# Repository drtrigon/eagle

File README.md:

## Projekte

Results of eagle and kicad CI from travis are stored in https://github.com/drtrigon/eagle/tree/result/pcb branch and linked/shown in https://github.com/drtrigon/sketchbook repo. See there and in [.travis.yml](.travis.yml) for more info.

(might make sense to split projects off into separate repos/submodules)

### N64TinyUSB

Order: make sure to select PCB Thickness 2mm and "Gold Fingers"!

based on boxtec.ch Helvetiny 1.0 PCB design:
* https://github.com/boxtec/helvetiny85
* https://playground.boxtec.ch/doku.php/arduino/attinyusb/helvetiny85

#### code/firmware (design based on attiny45 n64-usb)

Built using the attiny45 n64-usb AVR source files. Works out of the box but emulates 1 device only (that contains both controller).

https://github.com/drtrigon/sketchbook/tree/master/cli/n64dual_tiny45

#### Hint: Order PCB directly

Upload the GERBER files below to https://jlcpcb.com/quote and order.

* Helvetiny85: https://github.com/drtrigon/eagle/blob/master/projects/HelveTiny_1.0_GERBER.zip
* Floweronly Arduino Shield: https://github.com/boxtec/floweronly/blob/master/floweronly_v1.0_GERBER.zip

### Drone_MultiWii / FlightController

### arduino-papilio_1-WireSniffer_Rev1

### DACRackUnit

## Setup

I would like to use features like CI (continous integration) keep a copy/mirror on e.g. github and more.

Maintaining a copy/mirror (more precise: with 2 remotes overloaded origin) on GitHub also allows
to use GitLab and GitHub together and by that all the nice featurs on GitHub.
See also; https://steveperkins.com/migrating-projects-from-github-to-gitlab/

"Option 2: Overload Origin with Both Remotes (needs one single pull/push only)"; in order to clone
and set this repo up use:
```
$ git clone file://///data/mount/gvfs/smb-share:server=.../01git/eagle.git
$ cd eagle
$ git remote set-url --add origin https://github.com/drtrigon/eagle.git
```
you can check the settings with:
```
$ git remote -v
origin  /data/mount/gvfs/smb-share:server=.../01git/eagle.git/ (fetch)
origin  /data/mount/gvfs/smb-share:server=.../01git/eagle.git/ (push)
origin  https://github.com/drtrigon/eagle.git (push)
```

### Enable EDRC.ME for a Repository (for Eagle)
http://www.edrc.me/docs/

### Enable Travis CI for a Repository (for Eagle)
https://github.com/drtrigon/test-eagle-edrc/blob/master/.travis.yml (does not work reliably yet)

Login to Travis-CI using the GitHub account and enable Travis-CI for the given repo.

Add a .travis.yml file to your project, commit, pull/push and enjoy.

A word of caution; the travis run will at the end - if successfull - try to push the
results back to this repo.

### Further Info
EDRC.me: https://michaelblouin.ca/blog/2018/02/25/automate-design-rule-checks-autodesk-eagle/

gerber (travis or local python script): http://www.rocketnumbernine.com/2011/12/14/automating-gerbers-from-eagle
```
...
# create top copper (cmp), bottom copper (sol), top solder mask (stc), bottom solder mask (sts), {top} silkscreen (plc)
${EAGLE} -X -dGERBER_RS274X -o${outputfile}.cmp ${board} Top Pads Vias
${EAGLE} -X -dGERBER_RS274X -o${outputfile}.sol ${board} Bottom Pads Vias
#${EAGLE} -X -dGERBER_RS274X -o${outputfile}.mil ${board} Milling
${EAGLE} -X -dGERBER_RS274X -o${outputfile}.plc ${board} Dimension tPlace tNames
${EAGLE} -X -dGERBER_RS274X -o${outputfile}.stc ${board} tStop
${EAGLE} -X -dGERBER_RS274X -o${outputfile}.sts ${board} bStop
#${EAGLE} -X -dGERBER_RS274X -o${outputfile}.crc ${board} tCream
#${EAGLE} -X -dGERBER_RS274X -o${outputfile}.dpv ${board} Drills
#${EAGLE} -X -dGERBER_RS274X -o${outputfile}.drh ${board} Holes
...
```
(mill and drill needs: gerb274x-mill-drill.cam)

#### Generate schematic, PCB and GERBER from KiCAD (TODO)
* https://forum.kicad.info/t/generate-gerber-files-from-script/1853/15
* https://electronics.stackexchange.com/questions/390135/command-line-interface-for-kicad

## License

The content of this project itself is licensed under the [Creative Commons Attribution 3.0 license](http://creativecommons.org/licenses/by/3.0/us/deed.en_US), and the underlying source code used to format and display that content is licensed under the [MIT license](http://opensource.org/licenses/mit-license.php), see the [LICENSE](LICENSE.md) file for license rights and limitations (MIT).

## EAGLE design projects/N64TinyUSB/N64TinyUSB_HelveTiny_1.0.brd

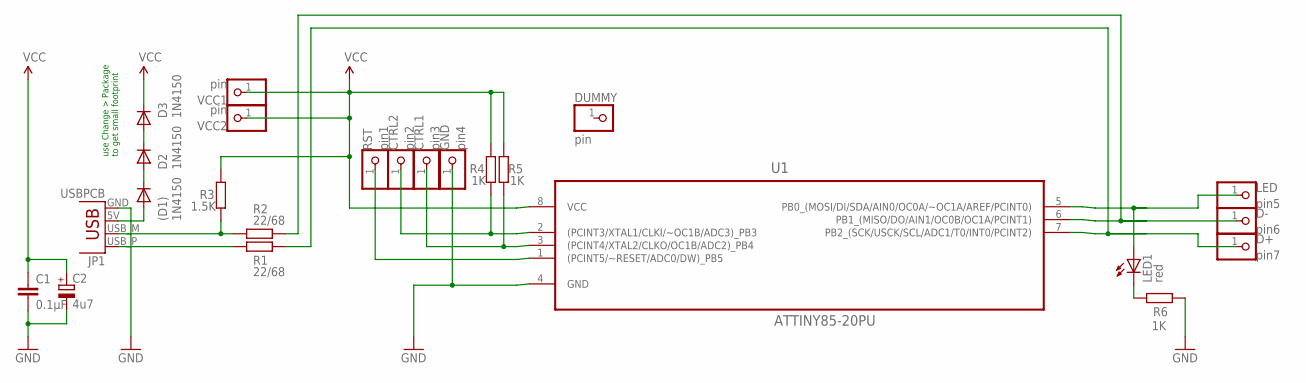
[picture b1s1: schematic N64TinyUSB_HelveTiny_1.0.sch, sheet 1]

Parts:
(D1): 1N4150; D-2.5
C1: 0.1μF; C025-024X044
C2: 4u7; E2,5-6E
CTRL1: pin3; 1X01
CTRL2: pin2; 1X01
D2, D3: 1N4150; D-2.5
D+: pin7; 1X01
D-: pin6; 1X01
DUMMY: pin; 1X01
GND: pin4; 1X01
JP1: USBPCB; USB-A-PCB
LED: pin5; 1X01
LED1: red; LED3MM
R1, R2: 22/68; 0207/7
R3: 1.5K; 0207/7
R4, R5, R6: 1K; 0207/7
RST: pin1; 1X01
U1: ATTINY85-20PU; DIP254P762X533-8
VCC1, VCC2: pin; 1X01

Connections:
CTRL1: CTRL1.1, R5.1, U1.3 ((PCINT4/XTAL2/CLKO/OC1B/ADC2)_PB4)
CTRL2: CTRL2.1, R4.1, U1.2 ((PCINT3/XTAL1/CLKI/~OC1B/ADC3)_PB3)
GND: C1.2, C2.-, GND.1, JP1.GND, R6.1, U1.4 (GND)
unnamed: JP1.USB_M (D-), R2.1, R3.1
unnamed: JP1.USB_P (D+), R1.1
unnamed: LED.1, LED1.A, U1.5 (PB0_(MOSI/DI/SDA/AIN0/OC0A/~OC1A/AREF/P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)
unnamed: D-.1, R2.2, U1.6 (PB1_(MISO/DO/AIN1/OC0B/OC1A/PCINT1))
unnamed: D+.1, R1.2, U1.7 (PB2_(SCK/USCK/SCL/ADC1/T0/INT0/PCINT2))
unnamed: (D1).A, JP1.5V (VBUS)
unnamed: (D1).C, D2.A
unnamed: D2.C, D3.A
unnamed: LED1.K (C), R6.2
RST: RST.1, U1.1 ((PCINT5/~RESET/ADC0/DW)_PB5)
VCC: C1.1, C2.+, D3.C, R3.2, R4.2, R5.2, U1.8 (VCC), VCC1.1, VCC2.1

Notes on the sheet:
use Change > Package to get small footprint

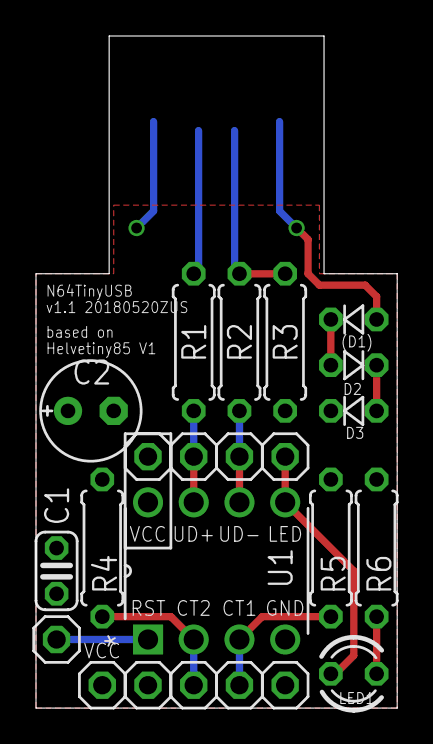
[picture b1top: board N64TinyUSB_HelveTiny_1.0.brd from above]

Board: 2 copper layers, 20.1 x 37.3 mm, 24 parts (1 on the bottom side), 14 nets.

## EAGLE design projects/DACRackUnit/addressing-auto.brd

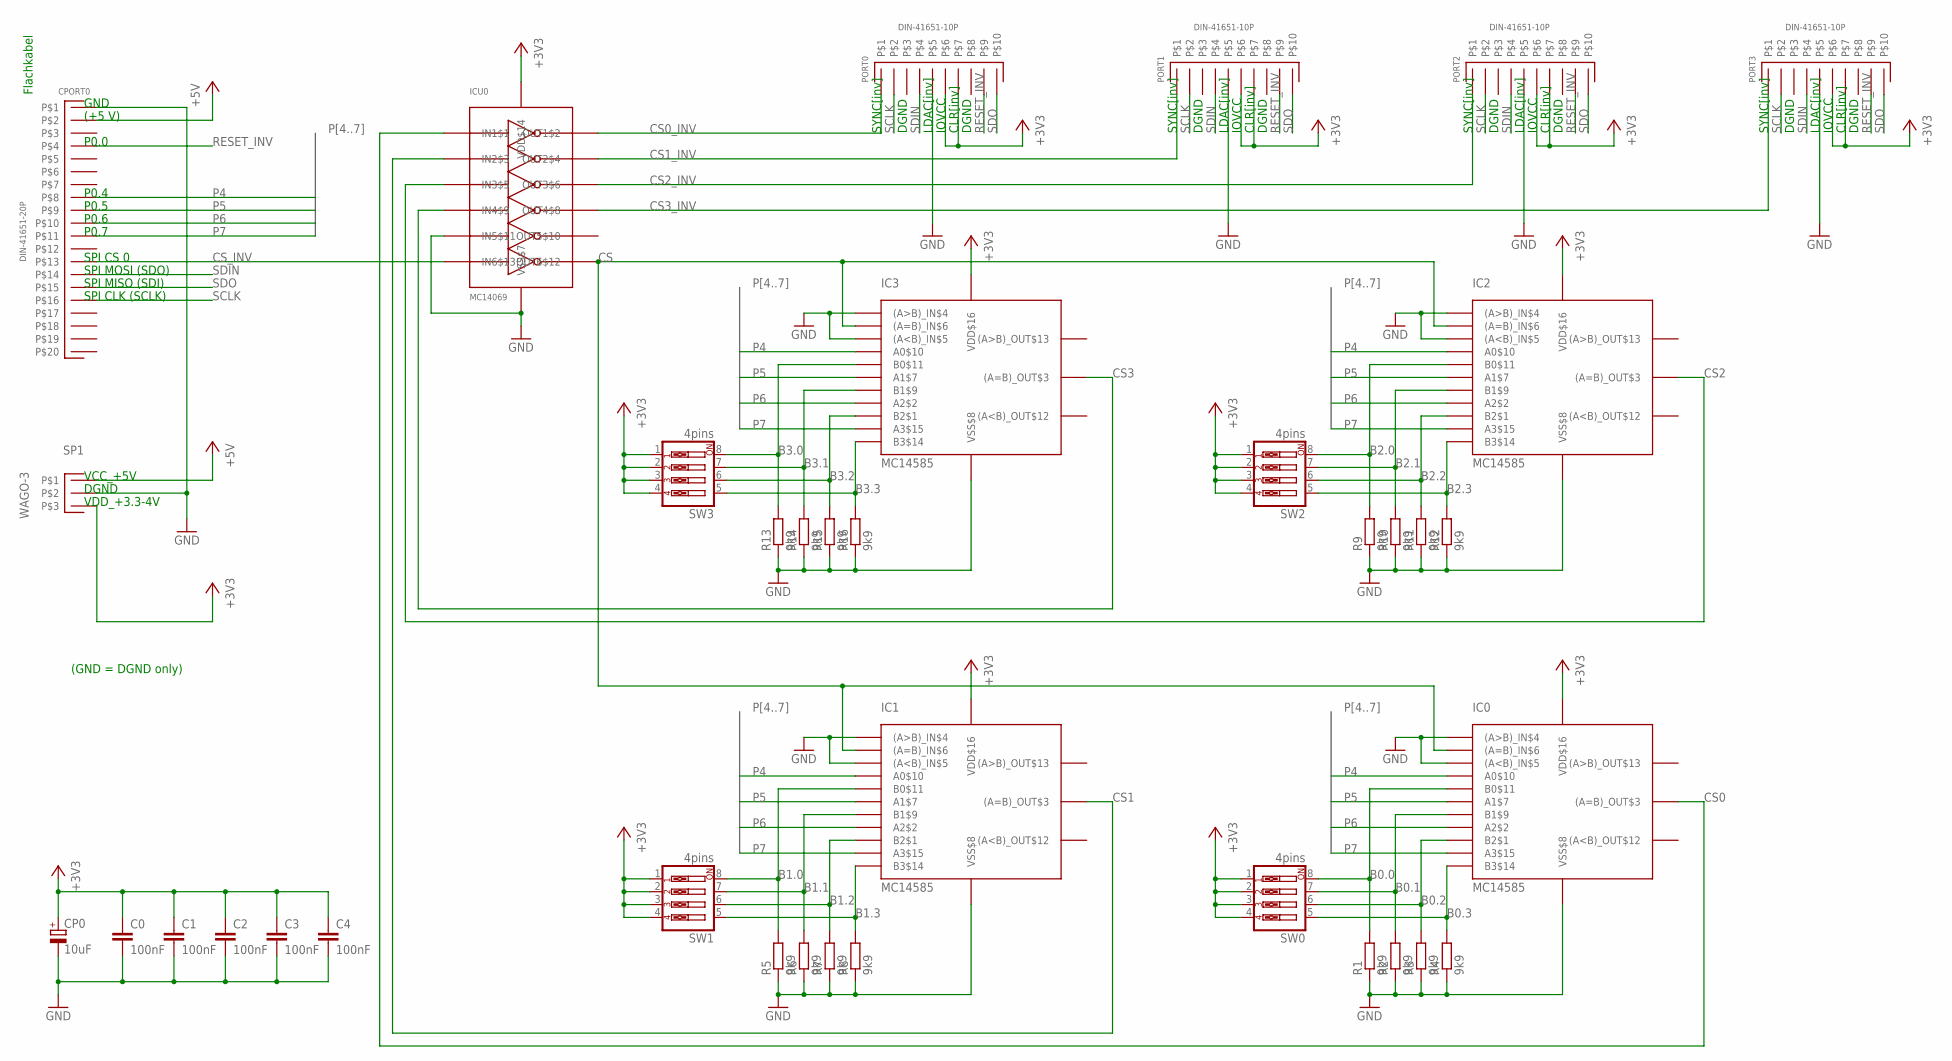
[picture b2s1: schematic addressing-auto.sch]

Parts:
C0, C1, C2, C3, C4: 100nF; C075-032X103
CP0: 10uF; B45181B
CPORT0: DIN-41651-20P
IC0, IC1, IC2, IC3: MC14585; PDIP-16
ICU0: MC14069; PDIP-14
PORT0, PORT1, PORT2, PORT3: DIN-41651-10P
R1, R2, R3, R4, R5, R6, R7, R8, R9, R10, R11, R12, R13, R14, R15, R16: 9k9; 0207/12
SP1: WAGO-3
SW0, SW1, SW2, SW3: 4pins; EDG-04

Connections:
+3V3: C0.1, C1.1, C2.1, C3.1, C4.1, CP0.+, IC0.VDD$16, IC1.VDD$16, IC2.VDD$16, IC3.VDD$16, ICU0.VDD$14, PORT0.P$6, PORT0.P$7, PORT1.P$6, PORT1.P$7, PORT2.P$6, PORT2.P$7, PORT3.P$6, PORT3.P$7, SP1.P$3, SW0.1, SW0.2, SW0.3, SW0.4, SW1.1, SW1.2, SW1.3, SW1.4, SW2.1, SW2.2, SW2.3, SW2.4, SW3.1, SW3.2, SW3.3, SW3.4
+5V: CPORT0.P$2, SP1.P$1
B0.0: IC0.B0$11, R1.2, SW0.8
B0.1: IC0.B1$9, R2.2, SW0.7
B0.2: IC0.B2$1, R3.2, SW0.6
B0.3: IC0.B3$14, R4.2, SW0.5
B1.0: IC1.B0$11, R5.2, SW1.8
B1.1: IC1.B1$9, R6.2, SW1.7
B1.2: IC1.B2$1, R7.2, SW1.6
B1.3: IC1.B3$14, R8.2, SW1.5
B2.0: IC2.B0$11, R9.2, SW2.8
B2.1: IC2.B1$9, R10.2, SW2.7
B2.2: IC2.B2$1, R11.2, SW2.6
B2.3: IC2.B3$14, R12.2, SW2.5
B3.0: IC3.B0$11, R13.2, SW3.8
B3.1: IC3.B1$9, R14.2, SW3.7
B3.2: IC3.B2$1, R15.2, SW3.6
B3.3: IC3.B3$14, R16.2, SW3.5
CS: IC0.(A=B)_IN$6, IC1.(A=B)_IN$6, IC2.(A=B)_IN$6, IC3.(A=B)_IN$6, ICU0.OUT6$12
CS0: IC0.(A=B)_OUT$3, ICU0.IN1$1
CS0_INV: ICU0.OUT1$2, PORT0.P$1
CS1: IC1.(A=B)_OUT$3, ICU0.IN2$3
CS1_INV: ICU0.OUT2$4, PORT1.P$1
CS2: IC2.(A=B)_OUT$3, ICU0.IN3$5
CS2_INV: ICU0.OUT3$6, PORT2.P$1
CS3: IC3.(A=B)_OUT$3, ICU0.IN4$9
CS3_INV: ICU0.OUT4$8, PORT3.P$1
CS_INV: CPORT0.P$13, ICU0.IN6$13
GND: C0.2, C1.2, C2.2, C3.2, C4.2, CP0.-, CPORT0.P$1, IC0.(A<B)_IN$5, IC0.(A>B)_IN$4, IC0.VSS$8, IC1.(A<B)_IN$5, IC1.(A>B)_IN$4, IC1.VSS$8, IC2.(A<B)_IN$5, IC2.(A>B)_IN$4, IC2.VSS$8, IC3.(A<B)_IN$5, IC3.(A>B)_IN$4, IC3.VSS$8, ICU0.IN5$11, ICU0.VSS$7, PORT0.P$5, PORT1.P$5, PORT2.P$5, PORT3.P$5, R1.1, R2.1, R3.1, R4.1, R5.1, R6.1, R7.1, R8.1, R9.1, R10.1, R11.1, R12.1, R13.1, R14.1, R15.1, R16.1, SP1.P$2
P4: CPORT0.P$8, IC0.A0$10, IC1.A0$10, IC2.A0$10, IC3.A0$10
P5: CPORT0.P$9, IC0.A1$7, IC1.A1$7, IC2.A1$7, IC3.A1$7
P6: CPORT0.P$10, IC0.A2$2, IC1.A2$2, IC2.A2$2, IC3.A2$2
P7: CPORT0.P$11, IC0.A3$15, IC1.A3$15, IC2.A3$15, IC3.A3$15
RESET_INV: CPORT0.P$4, PORT0.P$9, PORT1.P$9, PORT2.P$9, PORT3.P$9
SCLK: CPORT0.P$16, PORT0.P$2, PORT1.P$2, PORT2.P$2, PORT3.P$2
SDIN: CPORT0.P$14, PORT0.P$4, PORT1.P$4, PORT2.P$4, PORT3.P$4
SDO: CPORT0.P$15, PORT0.P$10, PORT1.P$10, PORT2.P$10, PORT3.P$10

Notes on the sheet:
GND
(+5 V)
P0.0
P0.4
P0.5
P0.6
P0.7
SPI CS 0
SPI MOSI (SDO)
SPI MISO (SDI)
SPI CLK (SCLK)
SYNC[inv]
DGND
LDAC[inv]
IOVCC
CLR[inv]
VCC_+5V
VDD_+3.3-4V
(GND = DGND only)
Flachkabel

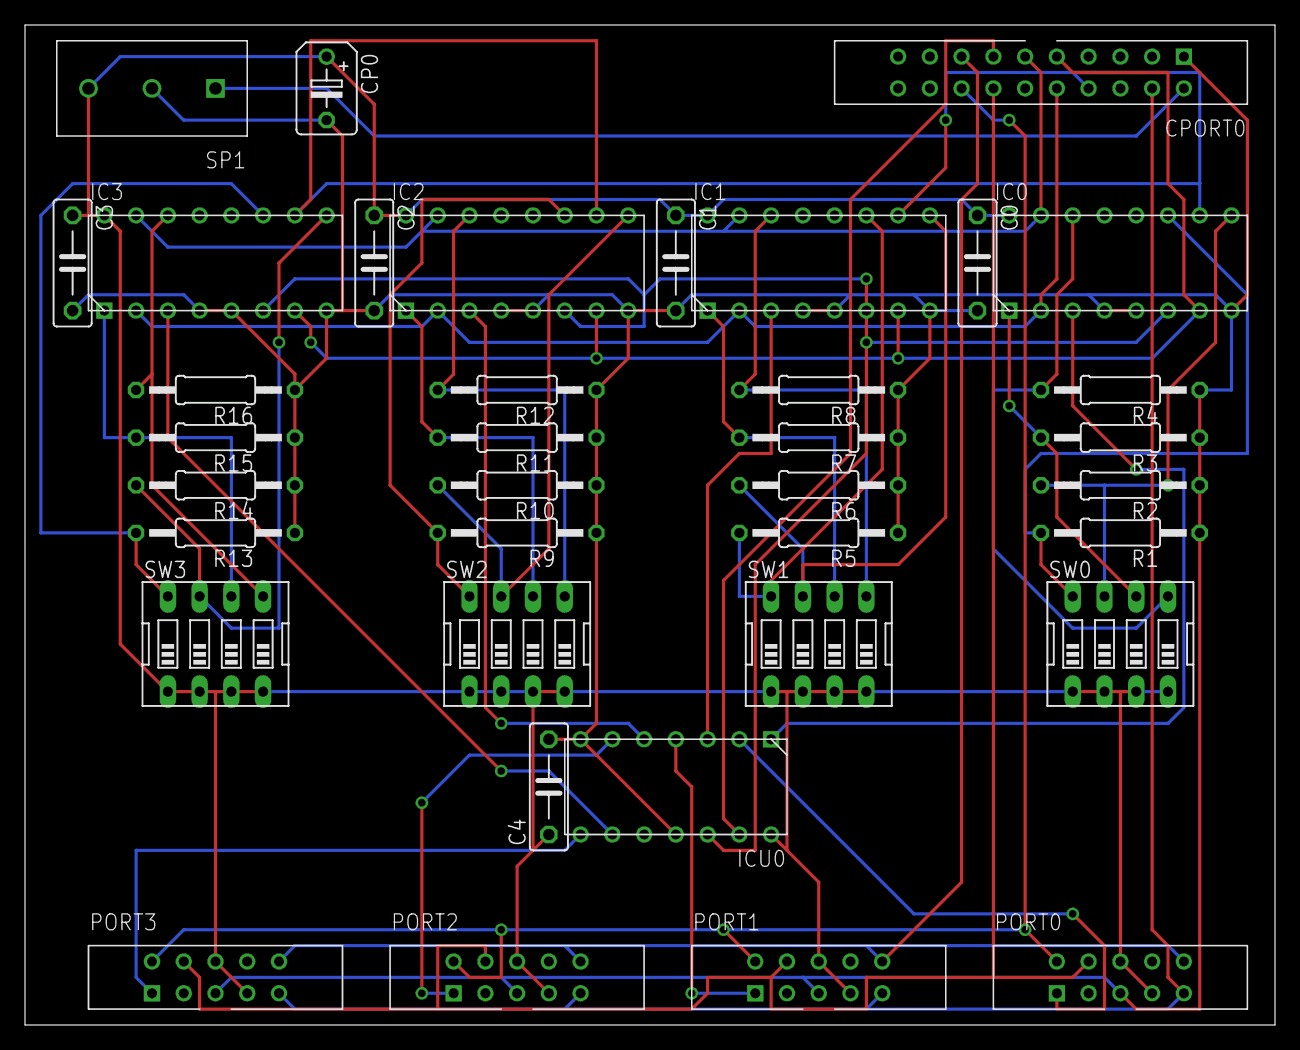
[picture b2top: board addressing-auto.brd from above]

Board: 2 copper layers, 100.0 x 80.0 mm, 37 parts (0 on the bottom side), 37 nets.

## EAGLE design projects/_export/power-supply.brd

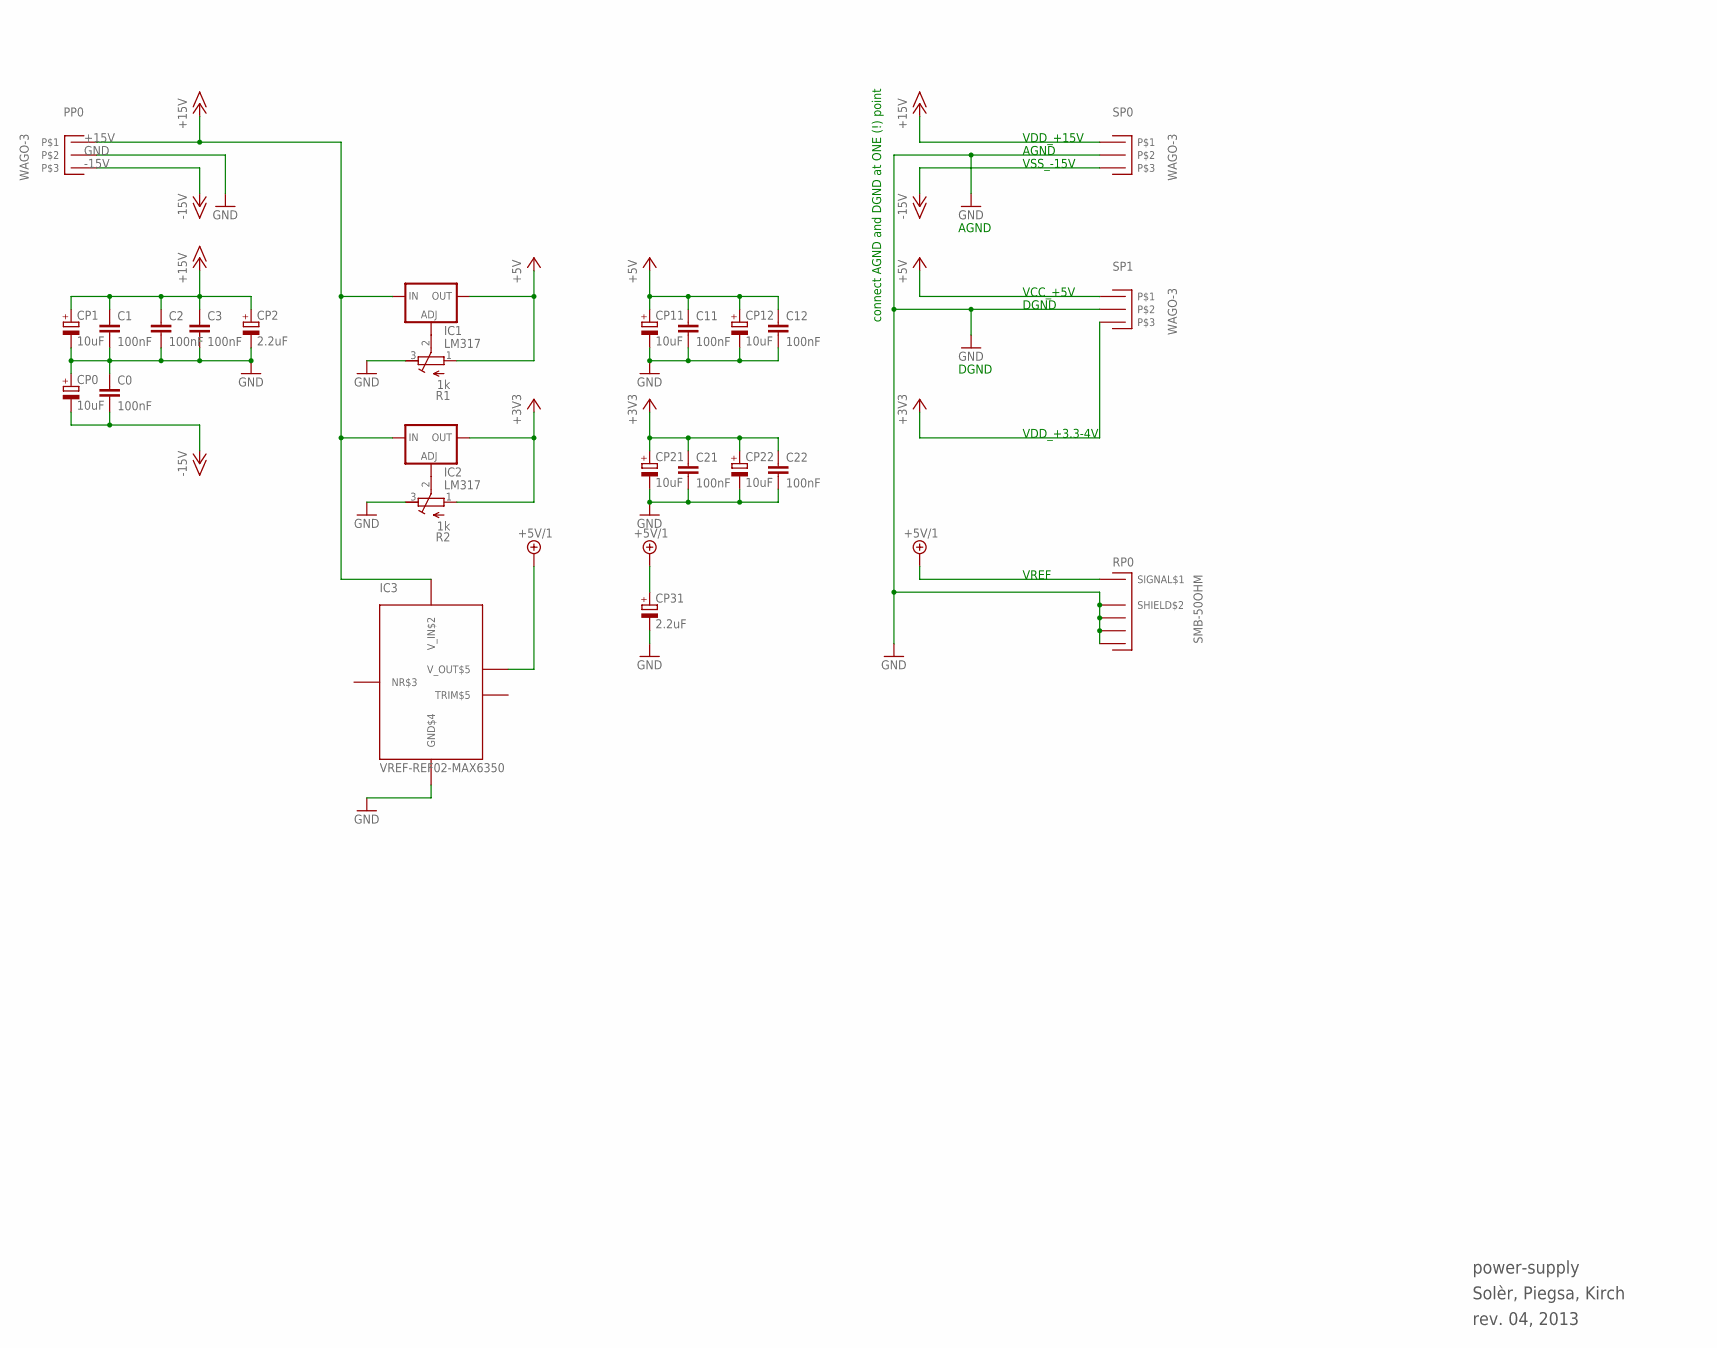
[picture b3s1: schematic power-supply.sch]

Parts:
C0, C1, C2, C3, C11, C12, C21, C22: 100nF; C050-025X075
CP0, CP1, CP11, CP12, CP21, CP22: 10uF; B45181B
CP2, CP31: 2.2uF; B45181B
IC1, IC2: LM317; 317TS
IC3: VREF-REF02-MAX6350; PDIP-8
PP0: WAGO-3
R1, R2: 1k; RTRIM3296Y
RP0: SMB-50OHM; B-30
SP0, SP1: WAGO-3

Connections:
+3V3: C21.1, C22.1, CP21.+, CP22.+, IC2.2 (OUT), R2.1 (A), SP1.P$3
+5V: C11.1, C12.1, CP11.+, CP12.+, IC1.2 (OUT), R1.1 (A), SP1.P$1
+5V/1: CP31.+, IC3.V_OUT$6 (V_OUT$5), RP0.P$1 (SIGNAL$1)
+15V: C1.1, C2.1, C3.1, CP1.+, CP2.+, IC1.3 (IN), IC2.3 (IN), IC3.V_IN$2, PP0.P$1, SP0.P$1
-15V: C0.2, CP0.-, PP0.P$3, SP0.P$3
GND: C0.1, C1.2, C2.2, C3.2, C11.2, C12.2, C21.2, C22.2, CP0.+, CP1.-, CP2.-, CP11.-, CP12.-, CP21.-, CP22.-, CP31.-, IC3.GND$4, PP0.P$2, R1.3 (E), R2.3 (E), RP0.P$2 (SHIELD$2), RP0.P$3 (SHIELD$3), RP0.P$4 (SHIELD$4), RP0.P$5 (SHIELD$5), SP0.P$2, SP1.P$2
unnamed: IC1.1 (ADJ), R1.2 (S)
unnamed: IC2.1 (ADJ), R2.2 (S)

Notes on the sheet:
VDD_+15V
AGND
VSS_-15V
VCC_+5V
DGND
VDD_+3.3-4V
VREF
connect AGND and DGND at ONE (!) point
power-supply
Solèr, Piegsa, Kirch
rev. 04, 2013

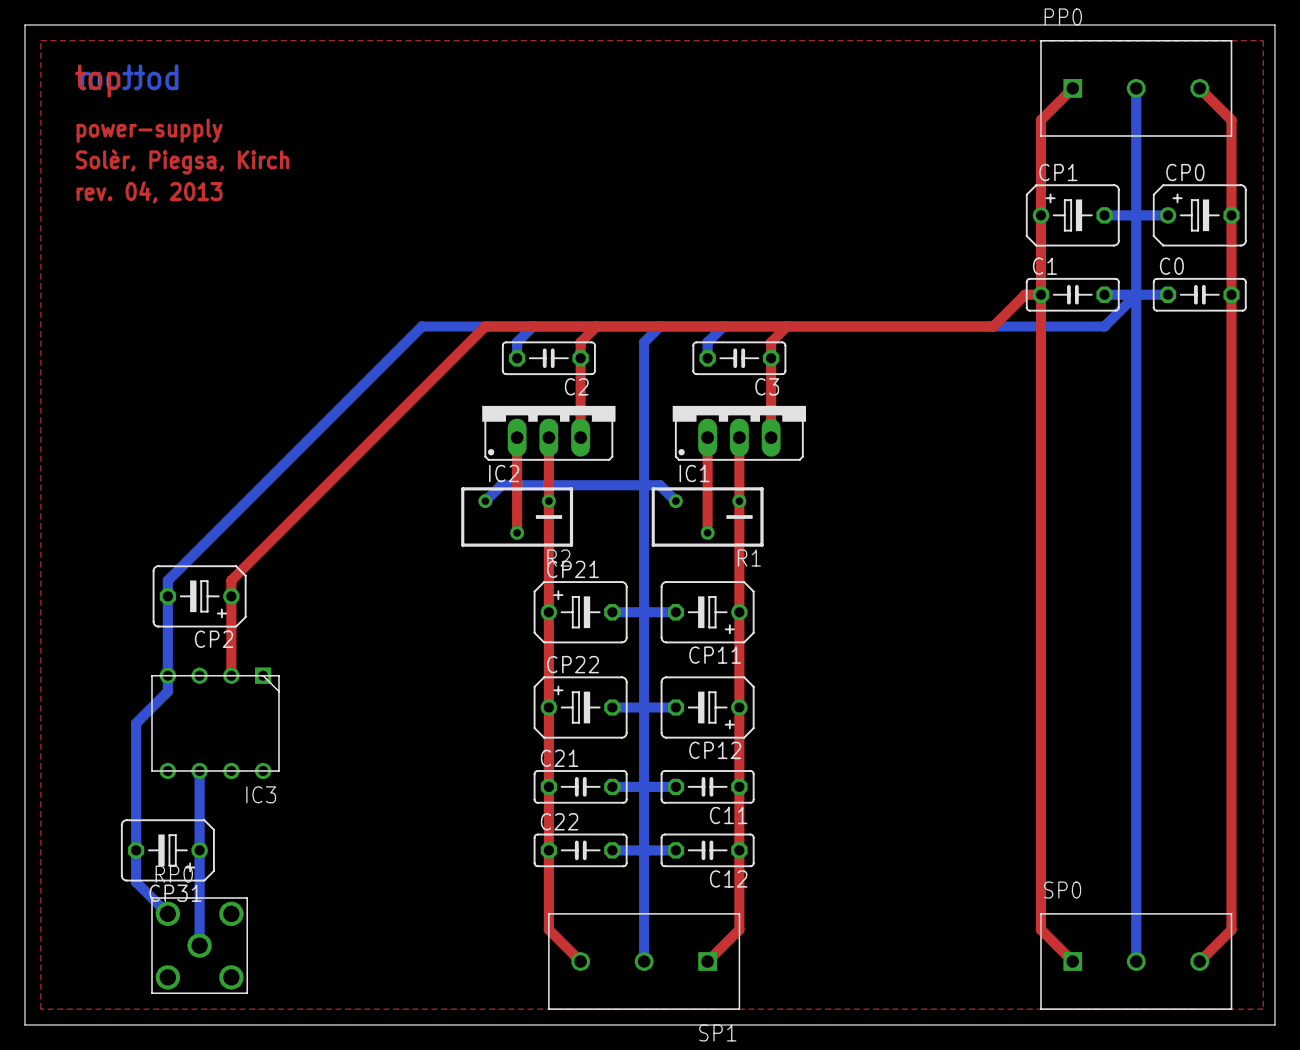
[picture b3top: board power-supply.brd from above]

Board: 2 copper layers, 100.0 x 80.0 mm, 25 parts (0 on the bottom side), 8 nets.

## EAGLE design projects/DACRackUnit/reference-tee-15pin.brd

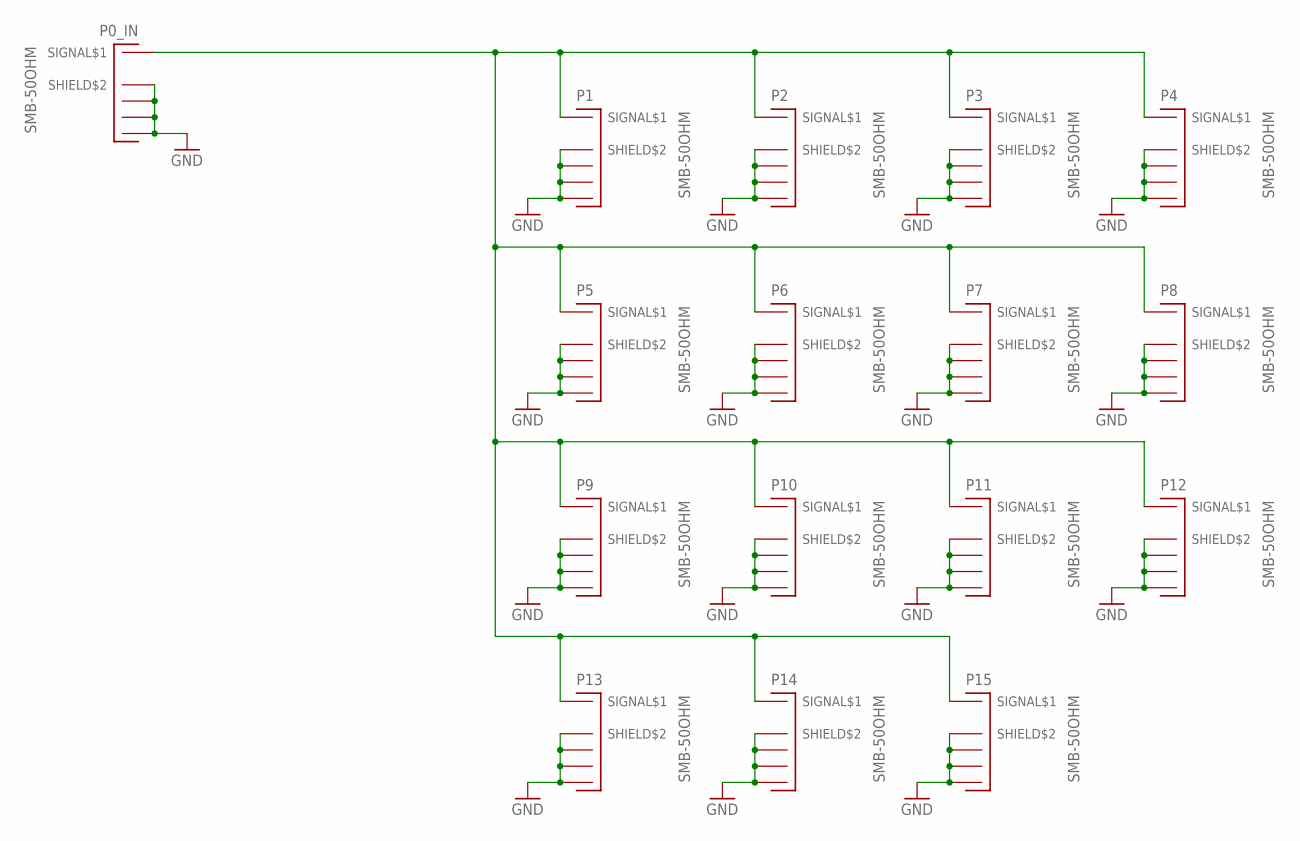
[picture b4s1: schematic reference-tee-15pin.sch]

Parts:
P0_IN, P1, P2, P3, P4, P5, P6, P7, P8, P9, P10, P11, P12, P13, P14, P15: SMB-50OHM; B-30

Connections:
GND: P0_IN.P$2 (SHIELD$2), P0_IN.P$3 (SHIELD$3), P0_IN.P$4 (SHIELD$4), P0_IN.P$5 (SHIELD$5), P1.P$2 (SHIELD$2), P1.P$3 (SHIELD$3), P1.P$4 (SHIELD$4), P1.P$5 (SHIELD$5), P2.P$2 (SHIELD$2), P2.P$3 (SHIELD$3), P2.P$4 (SHIELD$4), P2.P$5 (SHIELD$5), P3.P$2 (SHIELD$2), P3.P$3 (SHIELD$3), P3.P$4 (SHIELD$4), P3.P$5 (SHIELD$5), P4.P$2 (SHIELD$2), P4.P$3 (SHIELD$3), P4.P$4 (SHIELD$4), P4.P$5 (SHIELD$5), P5.P$2 (SHIELD$2), P5.P$3 (SHIELD$3), P5.P$4 (SHIELD$4), P5.P$5 (SHIELD$5), P6.P$2 (SHIELD$2), P6.P$3 (SHIELD$3), P6.P$4 (SHIELD$4), P6.P$5 (SHIELD$5), P7.P$2 (SHIELD$2), P7.P$3 (SHIELD$3), P7.P$4 (SHIELD$4), P7.P$5 (SHIELD$5), P8.P$2 (SHIELD$2), P8.P$3 (SHIELD$3), P8.P$4 (SHIELD$4), P8.P$5 (SHIELD$5), P9.P$2 (SHIELD$2), P9.P$3 (SHIELD$3), P9.P$4 (SHIELD$4), P9.P$5 (SHIELD$5), P10.P$2 (SHIELD$2), P10.P$3 (SHIELD$3), P10.P$4 (SHIELD$4), P10.P$5 (SHIELD$5), P11.P$2 (SHIELD$2), P11.P$3 (SHIELD$3), P11.P$4 (SHIELD$4), P11.P$5 (SHIELD$5), P12.P$2 (SHIELD$2), P12.P$3 (SHIELD$3), P12.P$4 (SHIELD$4), P12.P$5 (SHIELD$5), P13.P$2 (SHIELD$2), P13.P$3 (SHIELD$3), P13.P$4 (SHIELD$4), P13.P$5 (SHIELD$5), P14.P$2 (SHIELD$2), P14.P$3 (SHIELD$3), P14.P$4 (SHIELD$4), P14.P$5 (SHIELD$5), P15.P$2 (SHIELD$2), P15.P$3 (SHIELD$3), P15.P$4 (SHIELD$4), P15.P$5 (SHIELD$5)
unnamed: P0_IN.P$1 (SIGNAL$1), P1.P$1 (SIGNAL$1), P2.P$1 (SIGNAL$1), P3.P$1 (SIGNAL$1), P4.P$1 (SIGNAL$1), P5.P$1 (SIGNAL$1), P6.P$1 (SIGNAL$1), P7.P$1 (SIGNAL$1), P8.P$1 (SIGNAL$1), P9.P$1 (SIGNAL$1), P10.P$1 (SIGNAL$1), P11.P$1 (SIGNAL$1), P12.P$1 (SIGNAL$1), P13.P$1 (SIGNAL$1), P14.P$1 (SIGNAL$1), P15.P$1 (SIGNAL$1)

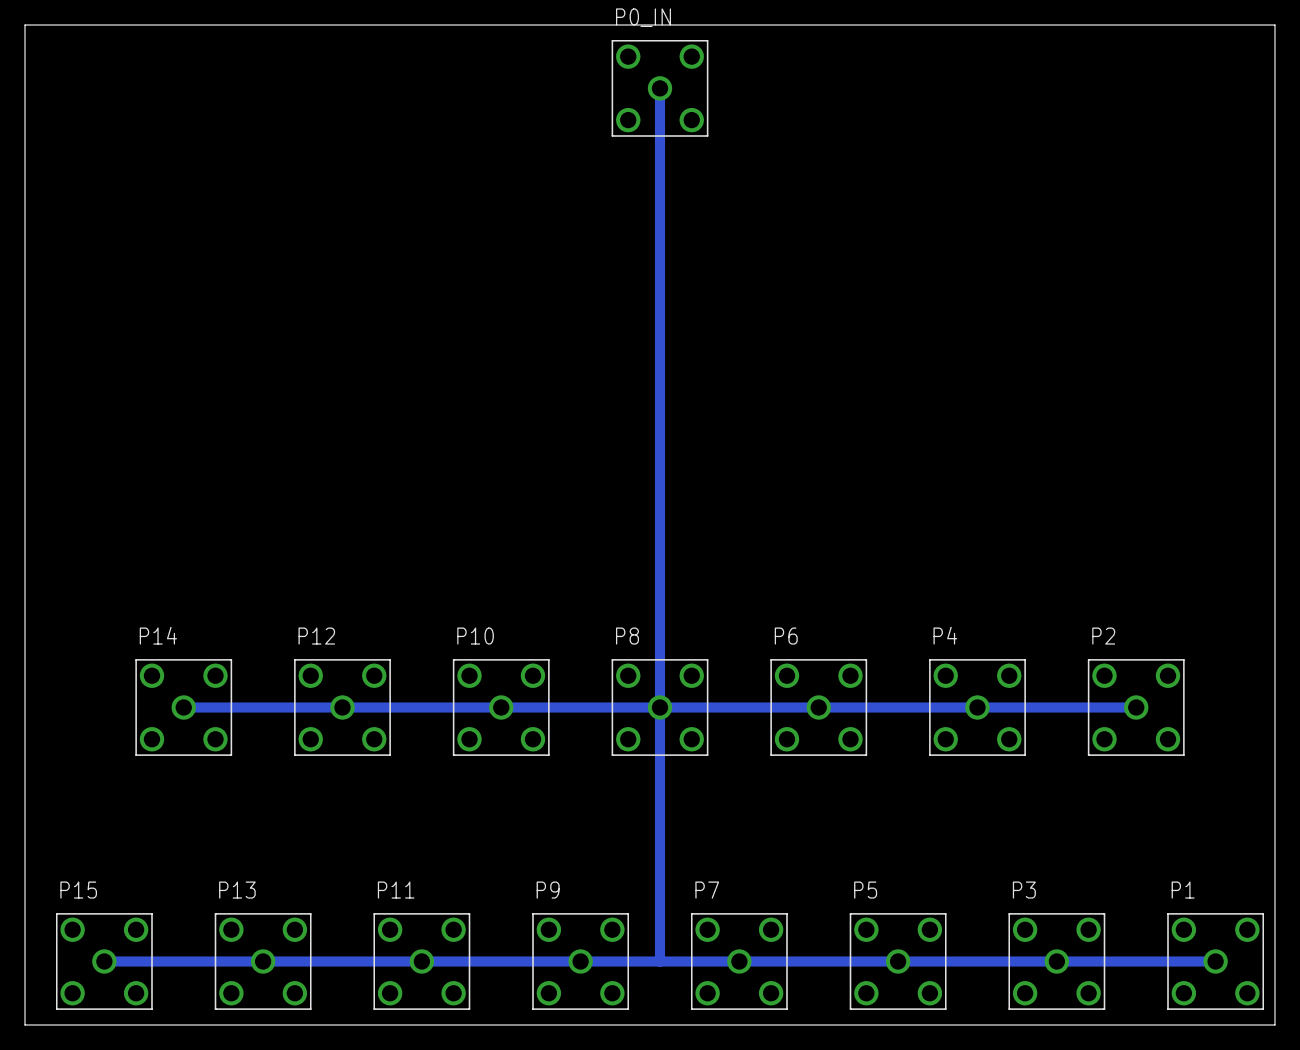
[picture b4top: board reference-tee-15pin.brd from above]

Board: 2 copper layers, 100.0 x 80.0 mm, 16 parts (0 on the bottom side), 2 nets.

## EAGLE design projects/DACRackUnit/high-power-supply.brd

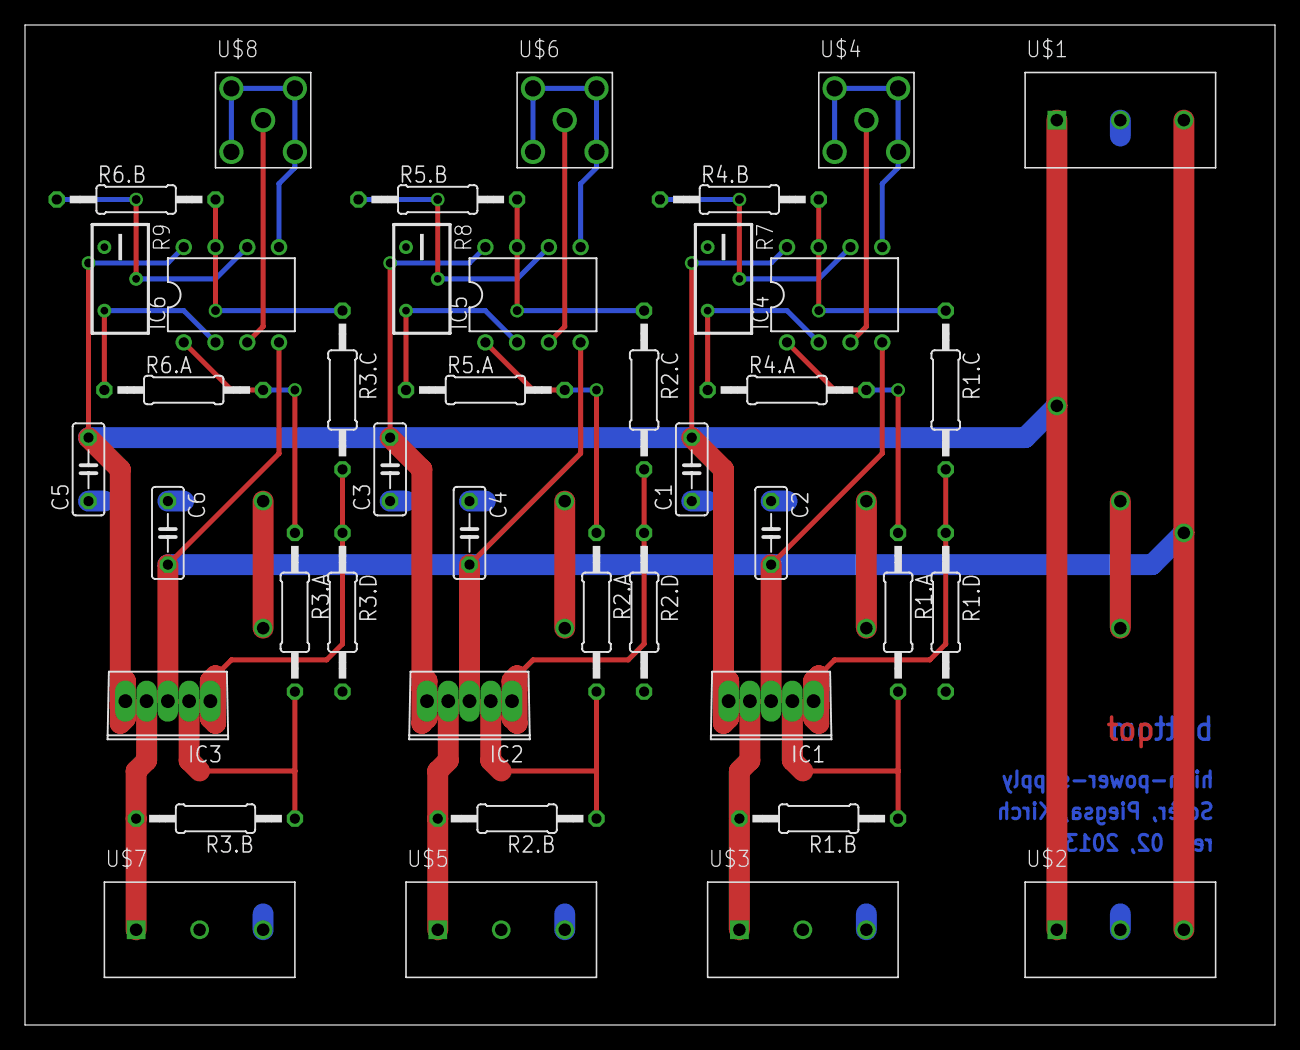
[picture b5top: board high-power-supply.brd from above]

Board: 2 copper layers, 100.0 x 80.0 mm, 41 parts (0 on the bottom side), 30 nets.

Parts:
C1, C2, C3, C4, C5, C6: 10muF; C050-025X075
IC1, IC2, IC3: OPA544T; TO220-G5
IC4, IC5, IC6: LM358N; DIL08
R1.A, R1.B, R1.C, R1.D, R2.A, R2.B, R2.C, R2.D, R3.A, R3.B, R3.C, R3.D: 25k ?; 0207/12
R4.A, R4.B, R5.A, R5.B, R6.A, R6.B: 10k ?; 0207/12
R7, R8, R9: 1M ?; RTRIM3296Y
U$1, U$2, U$3, U$5, U$7: WAGO-3
U$4, U$6, U$8: SMB-50OHM; B-30

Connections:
+15V: C1.2, C3.2, C5.2, IC1.5, IC2.5, IC3.5, IC4.8, IC5.8, IC6.8, U$1.P$1, U$2.P$1
+V1: IC4.3, U$4.P$1
+V2: IC5.3, U$6.P$1
+V3: IC6.3, U$8.P$1
-15V: C2.2, C4.2, C6.2, IC1.3, IC2.3, IC3.3, IC4.4, IC5.4, IC6.4, U$1.P$3, U$2.P$3
-V1: IC4.5, U$4.P$2, U$4.P$3, U$4.P$4, U$4.P$5
-V2: IC5.5, U$6.P$2, U$6.P$3, U$6.P$4, U$6.P$5
-V3: IC6.5, U$8.P$2, U$8.P$3, U$8.P$4, U$8.P$5
GND: C1.1, C2.1, C3.1, C4.1, C5.1, C6.1, R1.D.2, R2.D.2, R3.D.2, U$1.P$2, U$2.P$2, U$3.P$3, U$5.P$3, U$7.P$3
unnamed: IC1.2, R1.A.2, R1.B.1
unnamed: IC1.1, R1.C.2, R1.D.1
unnamed: IC4.2, R4.A.1, R7.3
unnamed: IC4.1, R1.A.1, R4.A.2
unnamed: IC4.6, R4.B.1, R7.2
unnamed: IC4.7, R1.C.1, R4.B.2
unnamed: IC5.2, R5.A.1, R8.3
unnamed: IC5.1, R2.A.1, R5.A.2
unnamed: IC5.6, R5.B.1, R8.2
unnamed: IC5.7, R2.C.1, R5.B.2
unnamed: IC2.2, R2.A.2, R2.B.1
unnamed: IC2.1, R2.C.2, R2.D.1
unnamed: IC6.2, R6.A.1, R9.3
unnamed: IC6.1, R3.A.1, R6.A.2
unnamed: IC6.6, R6.B.1, R9.2
unnamed: IC6.7, R3.C.1, R6.B.2
unnamed: IC3.2, R3.A.2, R3.B.1
unnamed: IC3.1, R3.C.2, R3.D.1
VOUT1: IC1.4, R1.B.2, U$3.P$1
VOUT2: IC2.4, R2.B.2, U$5.P$1
VOUT3: IC3.4, R3.B.2, U$7.P$1

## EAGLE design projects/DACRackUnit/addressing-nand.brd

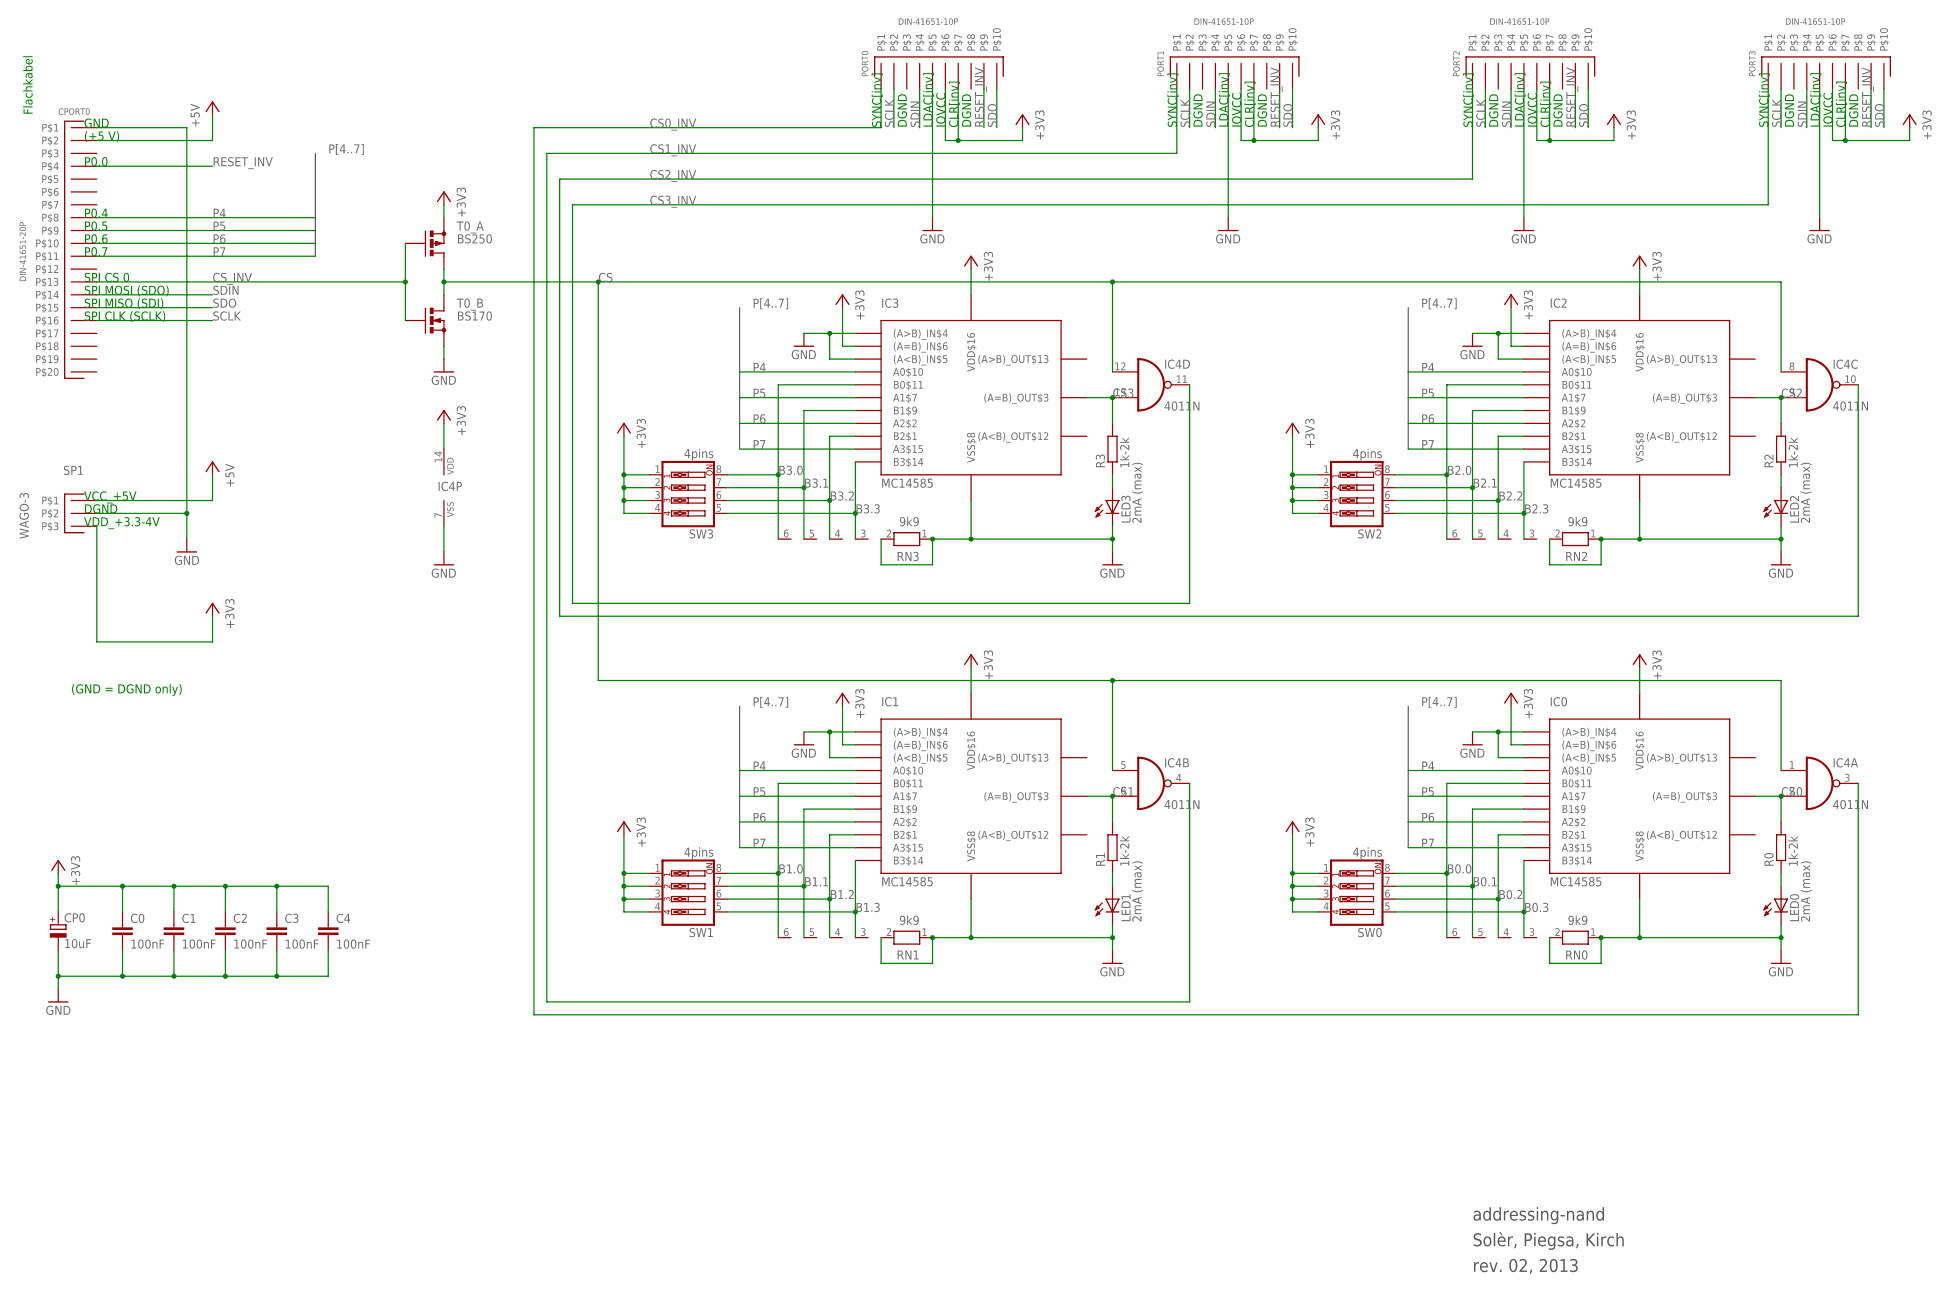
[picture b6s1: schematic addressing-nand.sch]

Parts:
C0, C1, C2, C3, C4: 100nF; C050-025X075
CP0: 10uF; B45181B
CPORT0: DIN-41651-20P
IC0, IC1, IC2, IC3: MC14585; PDIP-16
IC4: 4011N; DIL14
LED0, LED1, LED2, LED3: 2mA (max); LED3MM
PORT0, PORT1, PORT2, PORT3: DIN-41651-10P
R0, R1, R2, R3: 1k-2k; 0207/2V
RN0, RN1, RN2, RN3: 9k9; RN-6
SP1: WAGO-3
SW0, SW1, SW2, SW3: 4pins; EDG-04
T0_A: BS250; SOT54E
T0_B: BS170; SOT54E

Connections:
+3V3: C0.1, C1.1, C2.1, C3.1, C4.1, CP0.+, IC0.(A=B)_IN$6, IC0.VDD$16, IC1.(A=B)_IN$6, IC1.VDD$16, IC2.(A=B)_IN$6, IC2.VDD$16, IC3.(A=B)_IN$6, IC3.VDD$16, IC4.14 (VDD), PORT0.P$6, PORT0.P$7, PORT1.P$6, PORT1.P$7, PORT2.P$6, PORT2.P$7, PORT3.P$6, PORT3.P$7, SP1.P$3, SW0.1, SW0.2, SW0.3, SW0.4, SW1.1, SW1.2, SW1.3, SW1.4, SW2.1, SW2.2, SW2.3, SW2.4, SW3.1, SW3.2, SW3.3, SW3.4, T0_A.S
+5V: CPORT0.P$2, SP1.P$1
B0.0: IC0.B0$11, RN0.6, SW0.8
B0.1: IC0.B1$9, RN0.5, SW0.7
B0.2: IC0.B2$1, RN0.4, SW0.6
B0.3: IC0.B3$14, RN0.3, SW0.5
B1.0: IC1.B0$11, RN1.6, SW1.8
B1.1: IC1.B1$9, RN1.5, SW1.7
B1.2: IC1.B2$1, RN1.4, SW1.6
B1.3: IC1.B3$14, RN1.3, SW1.5
B2.0: IC2.B0$11, RN2.6, SW2.8
B2.1: IC2.B1$9, RN2.5, SW2.7
B2.2: IC2.B2$1, RN2.4, SW2.6
B2.3: IC2.B3$14, RN2.3, SW2.5
B3.0: IC3.B0$11, RN3.6, SW3.8
B3.1: IC3.B1$9, RN3.5, SW3.7
B3.2: IC3.B2$1, RN3.4, SW3.6
B3.3: IC3.B3$14, RN3.3, SW3.5
CS: IC4.1 (I0), IC4.5 (I0), IC4.8 (I0), IC4.12 (I0), T0_A.D, T0_B.D
CS0: IC0.(A=B)_OUT$3, IC4.2 (I1), R0.2
CS0_INV: IC4.3 (O), PORT0.P$1
CS1: IC1.(A=B)_OUT$3, IC4.6 (I1), R1.2
CS1_INV: IC4.4 (O), PORT1.P$1
CS2: IC2.(A=B)_OUT$3, IC4.9 (I1), R2.2
CS2_INV: IC4.10 (O), PORT2.P$1
CS3: IC3.(A=B)_OUT$3, IC4.13 (I1), R3.2
CS3_INV: IC4.11 (O), PORT3.P$1
CS_INV: CPORT0.P$13, T0_A.G, T0_B.G
GND: C0.2, C1.2, C2.2, C3.2, C4.2, CP0.-, CPORT0.P$1, IC0.(A<B)_IN$5, IC0.(A>B)_IN$4, IC0.VSS$8, IC1.(A<B)_IN$5, IC1.(A>B)_IN$4, IC1.VSS$8, IC2.(A<B)_IN$5, IC2.(A>B)_IN$4, IC2.VSS$8, IC3.(A<B)_IN$5, IC3.(A>B)_IN$4, IC3.VSS$8, IC4.7 (VSS), LED0.K (C), LED1.K (C), LED2.K (C), LED3.K (C), PORT0.P$5, PORT1.P$5, PORT2.P$5, PORT3.P$5, RN0.1, RN0.2, RN1.1, RN1.2, RN2.1, RN2.2, RN3.1, RN3.2, SP1.P$2, T0_B.S
unnamed: LED1.A, R1.1
unnamed: LED0.A, R0.1
unnamed: LED2.A, R2.1
unnamed: LED3.A, R3.1
P4: CPORT0.P$8, IC0.A0$10, IC1.A0$10, IC2.A0$10, IC3.A0$10
P5: CPORT0.P$9, IC0.A1$7, IC1.A1$7, IC2.A1$7, IC3.A1$7
P6: CPORT0.P$10, IC0.A2$2, IC1.A2$2, IC2.A2$2, IC3.A2$2
P7: CPORT0.P$11, IC0.A3$15, IC1.A3$15, IC2.A3$15, IC3.A3$15
RESET_INV: CPORT0.P$4, PORT0.P$9, PORT1.P$9, PORT2.P$9, PORT3.P$9
SCLK: CPORT0.P$16, PORT0.P$2, PORT1.P$2, PORT2.P$2, PORT3.P$2
SDIN: CPORT0.P$14, PORT0.P$4, PORT1.P$4, PORT2.P$4, PORT3.P$4
SDO: CPORT0.P$15, PORT0.P$10, PORT1.P$10, PORT2.P$10, PORT3.P$10

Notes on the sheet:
GND
(+5 V)
P0.0
P0.4
P0.5
P0.6
P0.7
SPI CS 0
SPI MOSI (SDO)
SPI MISO (SDI)
SPI CLK (SCLK)
SYNC[inv]
DGND
LDAC[inv]
IOVCC
CLR[inv]
VCC_+5V
VDD_+3.3-4V
(GND = DGND only)
Flachkabel
addressing-nand
Solèr, Piegsa, Kirch
rev. 02, 2013

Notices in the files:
parts and their libraries:
SparkFun-Connectors: Licensing: Creative Commons ShareAlike 4.0 International - https://creativecommons.org/licenses/by-sa/4.0
